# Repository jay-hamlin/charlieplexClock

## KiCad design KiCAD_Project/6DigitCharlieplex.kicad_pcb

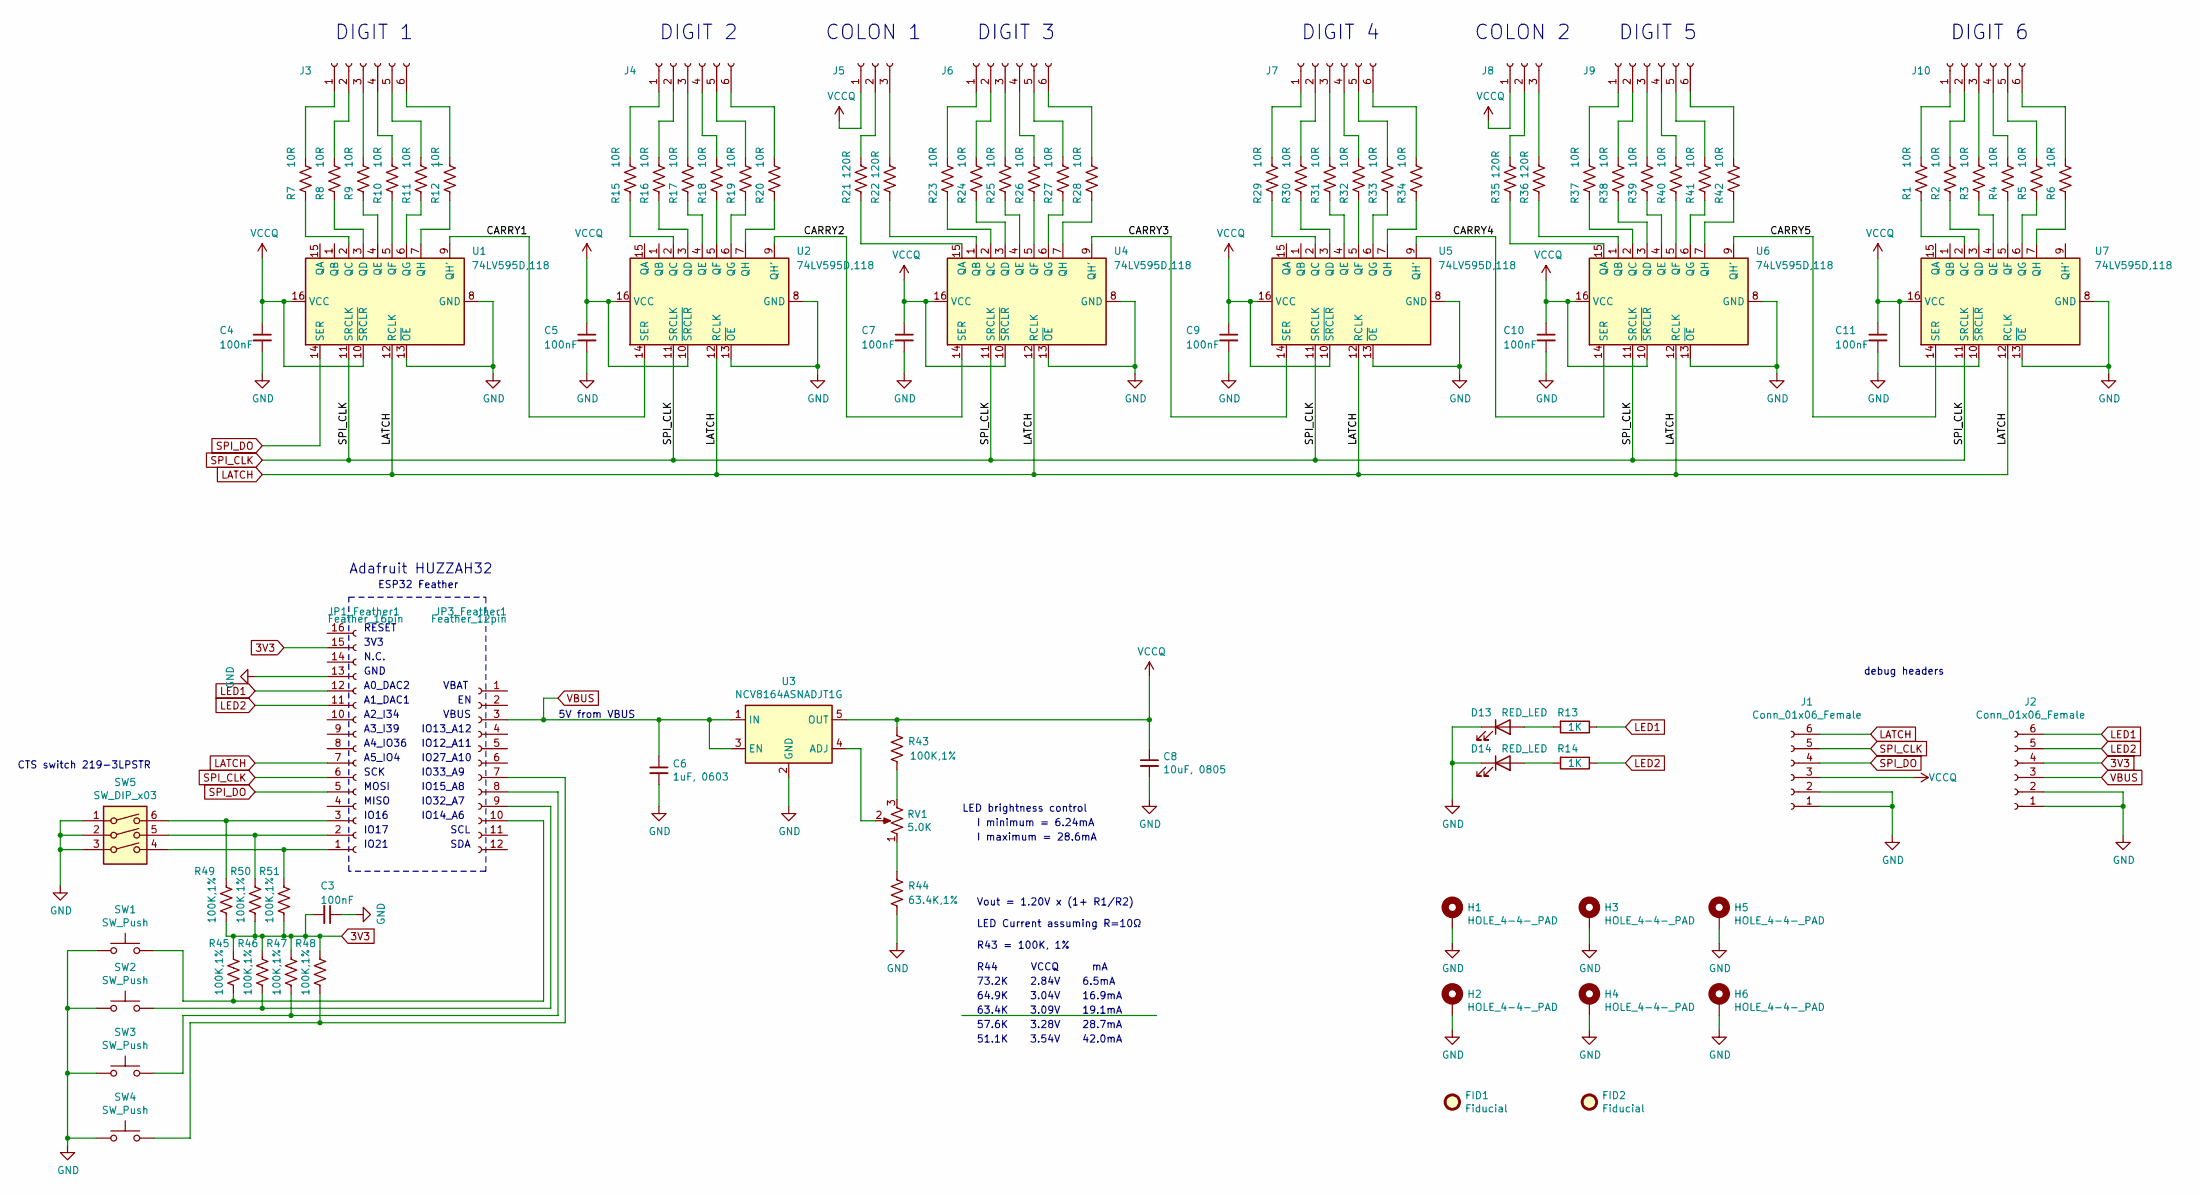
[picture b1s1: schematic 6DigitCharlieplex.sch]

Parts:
C3, C4, C5, C7, C9, C10, C11: 100nF; C_0603_1608Metric
C6: 1uF, 0603; C_0603_1608Metric
C8: 10uF, 0805; C_0805_2012Metric
D13, D14: RED_LED; LED_1206_3216Metric
FID1, FID2: Fiducial; Fiducial_0.5mm_Mask1.5mm
H1, H2, H3, H4, H5, H6: HOLE_4-4-_PAD; MountingHole_3.2mm_M3_Pad
J1, J2, J3, J4, J6, J7, J9, J10: Conn_01x06_Female; PinHeader_1x06_P2.54mm_Vertical
J5, J8: Conn_01x03_Female; PinHeader_1x03_P2.54mm_Vertical
JP1_Feather1: Feather_16pin; PinHeader_1x16_P2.54mm_Vertical
JP3_Feather1: Feather_12pin; PinHeader_1x12_P2.54mm_Vertical
R1, R2, R3, R4, R5, R6, R7, R8, R9, R10, R11, R12, R15, R16, R17, R18, R19, R20, R23, R24, R25, R26, R27, R28, R29, R30, R31, R32, R33, R34, R37, R38, R39, R40, R41, R42: 10R; R_0603_1608Metric
R13, R14: 1K; R_0603_1608Metric
R21, R22, R35, R36: 120R; R_0603_1608Metric
R43, R45, R46, R47, R48, R49, R50, R51: 100K,1%; R_0603_1608Metric
R44: 63.4K,1%; R_0603_1608Metric
RV1: 5.0K; Potentiometer_Bourns_3386C_Horizontal
SW1, SW2, SW3, SW4: SW_Push; SW_SPST_PTS645
SW5: SW_DIP_x03; DIP-6_W8.89mm_SMDSocket_LongPads
U1, U2, U4, U5, U6, U7: 74LV595D,118; SO-16_3.9x9.9mm_P1.27mm
U3: NCV8164ASNADJT1G; TSOT-23-5

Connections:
3V3: C3.2, J2.4, JP1_Feather1.15, R45.1, R46.1, R47.1, R48.1, R49.2, R50.2, R51.2
/CARRY1: U1.9 (QH'), U2.14 (SER)
/CARRY2: U2.9 (QH'), U4.14 (SER)
/CARRY3: U4.9 (QH'), U5.14 (SER)
/CARRY4: U5.9 (QH'), U6.14 (SER)
/CARRY5: U6.9 (QH'), U7.14 (SER)
GND: C3.1, C4.2, C5.2, C6.2, C7.2, C8.2, C9.2, C10.2, C11.2, D13.1 (K), D14.1 (K), H1.1, H2.1, H3.1, H4.1, H5.1, H6.1, J1.1, J1.2, J2.1, J2.2, JP1_Feather1.13, R44.2, SW1.1, SW2.1, SW3.1, SW4.1, SW5.1, SW5.2, SW5.3, U1.8 (GND), U1.13 (~OE), U2.8 (GND), U2.13 (~OE), U3.2 (GND), U4.8 (GND), U4.13 (~OE), U5.8 (GND), U5.13 (~OE), U6.8 (GND), U6.13 (~OE), U7.8 (GND), U7.13 (~OE)
LATCH: J1.6, JP1_Feather1.7, U1.12 (RCLK), U2.12 (RCLK), U4.12 (RCLK), U5.12 (RCLK), U6.12 (RCLK), U7.12 (RCLK)
LED1: J2.6, JP1_Feather1.12, R13.1
LED2: J2.5, JP1_Feather1.11, R14.1
unnamed: D13.2 (A), R13.2
unnamed: D14.2 (A), R14.2
unnamed: J3.1, R7.1
unnamed: J3.2, R8.1
unnamed: J3.3, R9.1
unnamed: J3.4, R10.1
unnamed: J3.5, R11.1
unnamed: J3.6, R12.1
unnamed: J4.1, R15.1
unnamed: J4.2, R16.1
unnamed: J4.3, R17.1
unnamed: J4.4, R18.1
unnamed: J4.5, R19.1
unnamed: J4.6, R20.1
unnamed: J5.2, R21.1
unnamed: J5.3, R22.1
unnamed: J6.1, R23.1
unnamed: J6.2, R24.1
unnamed: J6.3, R25.1
unnamed: J6.4, R26.1
unnamed: J6.5, R27.1
unnamed: J6.6, R28.1
unnamed: J7.1, R29.1
unnamed: J7.2, R30.1
unnamed: J7.3, R31.1
unnamed: J7.4, R32.1
unnamed: J7.5, R33.1
unnamed: J7.6, R34.1
unnamed: J8.2, R35.1
unnamed: J8.3, R36.1
unnamed: J9.1, R37.1
unnamed: J9.2, R38.1
unnamed: J9.3, R39.1
unnamed: J9.4, R40.1
unnamed: J9.5, R41.1
unnamed: J9.6, R42.1
unnamed: J10.1, R1.1
unnamed: J10.2, R2.1
unnamed: J10.3, R3.1
unnamed: J10.4, R4.1
unnamed: J10.5, R5.1
unnamed: J10.6, R6.1
unnamed: JP1_Feather1.1, R51.1, SW5.4
unnamed: JP1_Feather1.2, R50.1, SW5.5
unnamed: JP1_Feather1.3, R49.1, SW5.6
unnamed: JP3_Feather1.7, R48.2, SW4.2
unnamed: JP3_Feather1.8, R47.2, SW3.2
unnamed: JP3_Feather1.9, R46.2, SW2.2
unnamed: JP3_Feather1.10, R45.2, SW1.2
unnamed: R1.2, U7.2 (QC)
unnamed: R2.2, U7.3 (QD)
unnamed: R3.2, U7.4 (QE)
unnamed: R4.2, U7.5 (QF)
unnamed: R5.2, U7.6 (QG)
unnamed: R6.2, U7.7 (QH)
unnamed: R7.2, U1.2 (QC)
unnamed: R8.2, U1.3 (QD)
unnamed: R9.2, U1.4 (QE)
unnamed: R10.2, U1.5 (QF)
unnamed: R11.2, U1.6 (QG)
unnamed: R12.2, U1.7 (QH)
unnamed: R15.2, U2.2 (QC)
unnamed: R16.2, U2.3 (QD)
unnamed: R17.2, U2.4 (QE)
unnamed: R18.2, U2.5 (QF)
unnamed: R19.2, U2.6 (QG)
unnamed: R20.2, U2.7 (QH)
unnamed: R21.2, U4.15 (QA)
unnamed: R22.2, U4.1 (QB)
unnamed: R23.2, U4.2 (QC)
unnamed: R24.2, U4.3 (QD)
unnamed: R25.2, U4.4 (QE)
unnamed: R26.2, U4.5 (QF)
unnamed: R27.2, U4.6 (QG)
unnamed: R28.2, U4.7 (QH)
unnamed: R29.2, U5.2 (QC)
unnamed: R30.2, U5.3 (QD)
unnamed: R31.2, U5.4 (QE)
unnamed: R32.2, U5.5 (QF)
unnamed: R33.2, U5.6 (QG)
unnamed: R34.2, U5.7 (QH)
unnamed: R35.2, U6.15 (QA)
unnamed: R36.2, U6.1 (QB)
unnamed: R37.2, U6.2 (QC)
unnamed: R38.2, U6.3 (QD)
unnamed: R39.2, U6.4 (QE)
unnamed: R40.2, U6.5 (QF)
unnamed: R41.2, U6.6 (QG)
unnamed: R42.2, U6.7 (QH)
unnamed: R43.2, RV1.3
unnamed: R44.1, RV1.1
unnamed: RV1.2, U3.4 (ADJ)
SPI_CLK: J1.5, JP1_Feather1.6, U1.11 (SRCLK), U2.11 (SRCLK), U4.11 (SRCLK), U5.11 (SRCLK), U6.11 (SRCLK), U7.11 (SRCLK)
SPI_DO: J1.4, JP1_Feather1.5, U1.14 (SER)
VBUS: C6.1, J2.3, JP3_Feather1.3, U3.1 (IN), U3.3 (EN)
VCCQ: C4.1, C5.1, C7.1, C8.1, C9.1, C10.1, C11.1, J1.3, J5.1, J8.1, R43.1, U1.10 (~SRCLR), U1.16 (VCC), U2.10 (~SRCLR), U2.16 (VCC), U3.5 (OUT), U4.10 (~SRCLR), U4.16 (VCC), U5.10 (~SRCLR), U5.16 (VCC), U6.10 (~SRCLR), U6.16 (VCC), U7.10 (~SRCLR), U7.16 (VCC)

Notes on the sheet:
Adafruit HUZZAH32
ESP32 Feather
RESET
3V3
N.C.
GND
A0_DAC2
A1_DAC1
A2_I34
A3_I39
A4_IO36
A5_IO4
SCK
MOSI
MISO
IO16
IO17
IO21
VBAT
VBUS
IO13_A12
IO12_A11
IO27_A10
IO33_A9
IO15_A8
IO32_A7
IO14_A6
SCL
SDA
Vout = 1.20V x (1+ R1/R2)
LED Current assuming R=10Ω
R43 = 100K, 1%
R44 VCCQ mA
73.2K 2.84V 6.5mA
64.9K 3.04V 16.9mA
63.4K 3.09V 19.1mA
57.6K 3.28V 28.7mA
51.1K 3.54V 42.0mA
5V from VBUS
LED brightness control

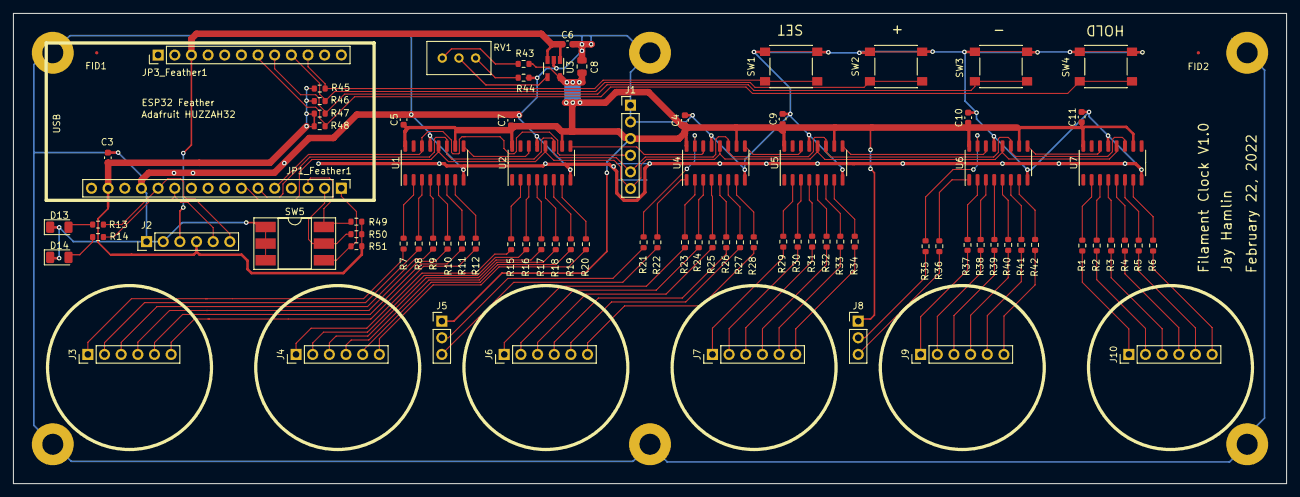
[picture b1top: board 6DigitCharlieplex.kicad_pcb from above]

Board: 2 copper layers, 194.1 x 71.7 mm, 95 parts (0 on the bottom side), 106 nets.

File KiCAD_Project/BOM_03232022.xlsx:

Reference | Count | Value | Footprint | Description | Manufacturer | MPN | Vendor | Vendor PN
C3,C4,C5,C7,C9,C10,C11 | 7 | 100nF | Capacitor_SMD:C_0603_1608Metric | CAP CER 0.1UF 16V X7R 0603 | Yageo | CC0603JRX7R7BB104 | Digikey | 311-1776-1-ND
C6 | 1 | 1uF, 0603 | Capacitor_SMD:C_0603_1608Metric | CAP CER 1UF 16V X7R 0603 | TDK | CGA3E1X7R1C105K080AC | Digikey | 445-12539-1-ND
C8 | 1 | 10uF, 0805 | Capacitor_SMD:C_0805_2012Metric | CAP CER 22UF 10V X5R 0805 | Murata | GRM21BR61A226ME51L | Digikey | 490-10511-1-ND
D13,D14 | 2 | RED_LED | LED_SMD:LED_1206_3216Metric | LED RED CLEAR 1206 SMD | Lite-ON | LTST-C150KRKT | Digikey | 160-1405-1-ND
R1,R2,R3,R4,R5,R6,R7,R8,R9,R10,R11,R12,R15,R16,R17,R18,R19,R20,R23,R24,R25,R26,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 | 36 | 10R | Resistor_SMD:R_0603_1608Metric | RES 10 OHM 1% 1/8W 0603 | Stackpole | RNCP0603FTD10R0 | Digikey | RNCP0603FTD10R0CT-ND
R21,R22,R35,R36 | 4 | 120R | Resistor_SMD:R_0603_1608Metric | RES 120 OHM 1% 1/10W 0603 | Yageo | RC0603FR-07120RL | Digikey | 311-120HRCT-ND
R13,R14 | 2 | 1K | Resistor_SMD:R_0603_1608Metric | RES SMD 1K OHM 1% 1/3W 0603 | Vishay | CRCW06031K00FKEAHP | Digikey | 541-1.00KSCT-ND
R44 | 1 | 63.4K,1% | Resistor_SMD:R_0603_1608Metric | RES 63.4K OHM 1% 1/10W 0603 | Stackpole | RMCF0603FT63K4 | Digikey | RMCF0603FT63K4CT-ND
R43,R45,R46,R47,R48,R49,R50,R51 | 8 | 100K,1% | Resistor_SMD:R_0603_1608Metric | RES 100K OHM 1% 1/16W 0603 | Yageo | AF0603FR-07100KL | Digikey | 13-AF0603FR-07100KLCT-ND
RV1 | 1 | 10.0K | Potentiometer_THT:Potentiometer_Bourns_3386C_Horizontal | TRIMMER 10K OHM 0.5W PC PIN SIDE | Bourns | 3386H-1-103LF | Digikey | 3386H-103LF-ND
J1,J2,J3,J4,J6,J7,J9,J10 | 8 | Conn_01x06_Female | Connector_PinHeader_2.54mm:PinHeader_1x06_P2.54mm_Vertical | CONN RCPT 6POS 0.1 TIN-LEAD PCB | 3M | 929974-01-06 | Digikey | 929974-01-06-ND
J5,J8 | 2 | Conn_01x03_Female | Connector_PinHeader_2.54mm:PinHeader_1x03_P2.54mm_Vertical | CONN RCPT 3POS 0.1 TIN-LEAD PCB | 3M | 929974-01-03 | Digikey | 929974-01-03-ND
JP1_Feather1 | 1 | Feather_16pin | Connector_PinHeader_2.54mm:PinHeader_1x16_P2.54mm_Vertical | CONN RCPT 16POS 0.1 TIN PCB | 3M | 929974-01-16-RK | Digikey | 929974E-01-16-ND
JP3_Feather1 | 1 | Feather_12pin | Connector_PinHeader_2.54mm:PinHeader_1x12_P2.54mm_Vertical | CONN RCPT 12POS 0.1 TIN PCB | 3M | 929974-01-12-RK | Digikey | 929974-01-12-ND
SW1,SW2,SW3,SW4 | 4 | SW_Push | Button_Switch_SMD:SW_SPST_PTS645 | SWITCH TACTILE SPST-NO 0.05A 12V | C&K | PTS645SH50SMTR92 LFS | Digikey | CKN9085CT-ND
SW5 | 1 | SW_DIP_x03 | Package_DIP:DIP-6_W8.89mm_SMDSocket_LongPads | SWITCH SLIDE DIP SPST 100MA 20V | CTS | 219-3LPSTR | Digikey | CT3115CT-ND
U1,U2,U4,U5,U6,U7 | 6 | 74LV595D,118 | Package_SO:SO-16_3.9x9.9mm_P1.27mm | IC 8BIT SHIFT REGISTER 16SOIC | Nexperia | 74LV595D,118 | Digikey | 1727-7348-1-ND
U3 | 1 | NCV8164ASNADJT1G | Package_TO_SOT_SMD:TSOT-23-5 | IC REG LIN POS ADJ 300MA 5TSOP | ON Semi | NCV8164ASNADJT1G | Digikey | 488-NCV8164ASNADJT1GCT-ND
HUZZAH32 | 1 | ESP32 Feather | custom | ESP32 Feather boar HUZZAH32 | Adafruit | 3405 | Adafruit | 3405
LED Filaments | 42 | 20mm,RED,3V |  | AliExpress https://www.aliexpress.com/item/1005003509056672.html?spm=a2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
Digit PCB | 1 |  |  | OSHPark, "After Dark", black substrate and clear soldermask
Main PCB | 1 |  |  | OSHPark, "After Dark", black substrate and clear soldermask

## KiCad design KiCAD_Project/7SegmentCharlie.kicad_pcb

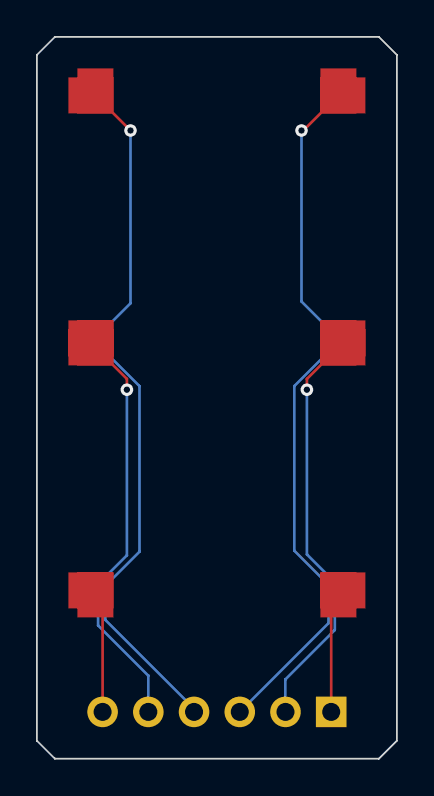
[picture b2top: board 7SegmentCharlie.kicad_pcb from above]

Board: 2 copper layers, 20.0 x 40.1 mm, 8 parts (0 on the bottom side), 6 nets.

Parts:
D1, D2, D3, D4, D5, D6, D7: LED; LEDFilament_12mm
J1: Conn_01x06_Female; PinHeader_1x06_P2.54mm_NoSilk

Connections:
unnamed: D1.1, D2.2, D4.2, J1.5
unnamed: D1.2, D3.2, J1.4
unnamed: D2.1, D5.2, J1.6
unnamed: D3.1, D6.2, J1.3
unnamed: D4.1, D6.1, D7.2, J1.2
unnamed: D5.1, D7.1, J1.1

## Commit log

2022-03-25 initial checkin
